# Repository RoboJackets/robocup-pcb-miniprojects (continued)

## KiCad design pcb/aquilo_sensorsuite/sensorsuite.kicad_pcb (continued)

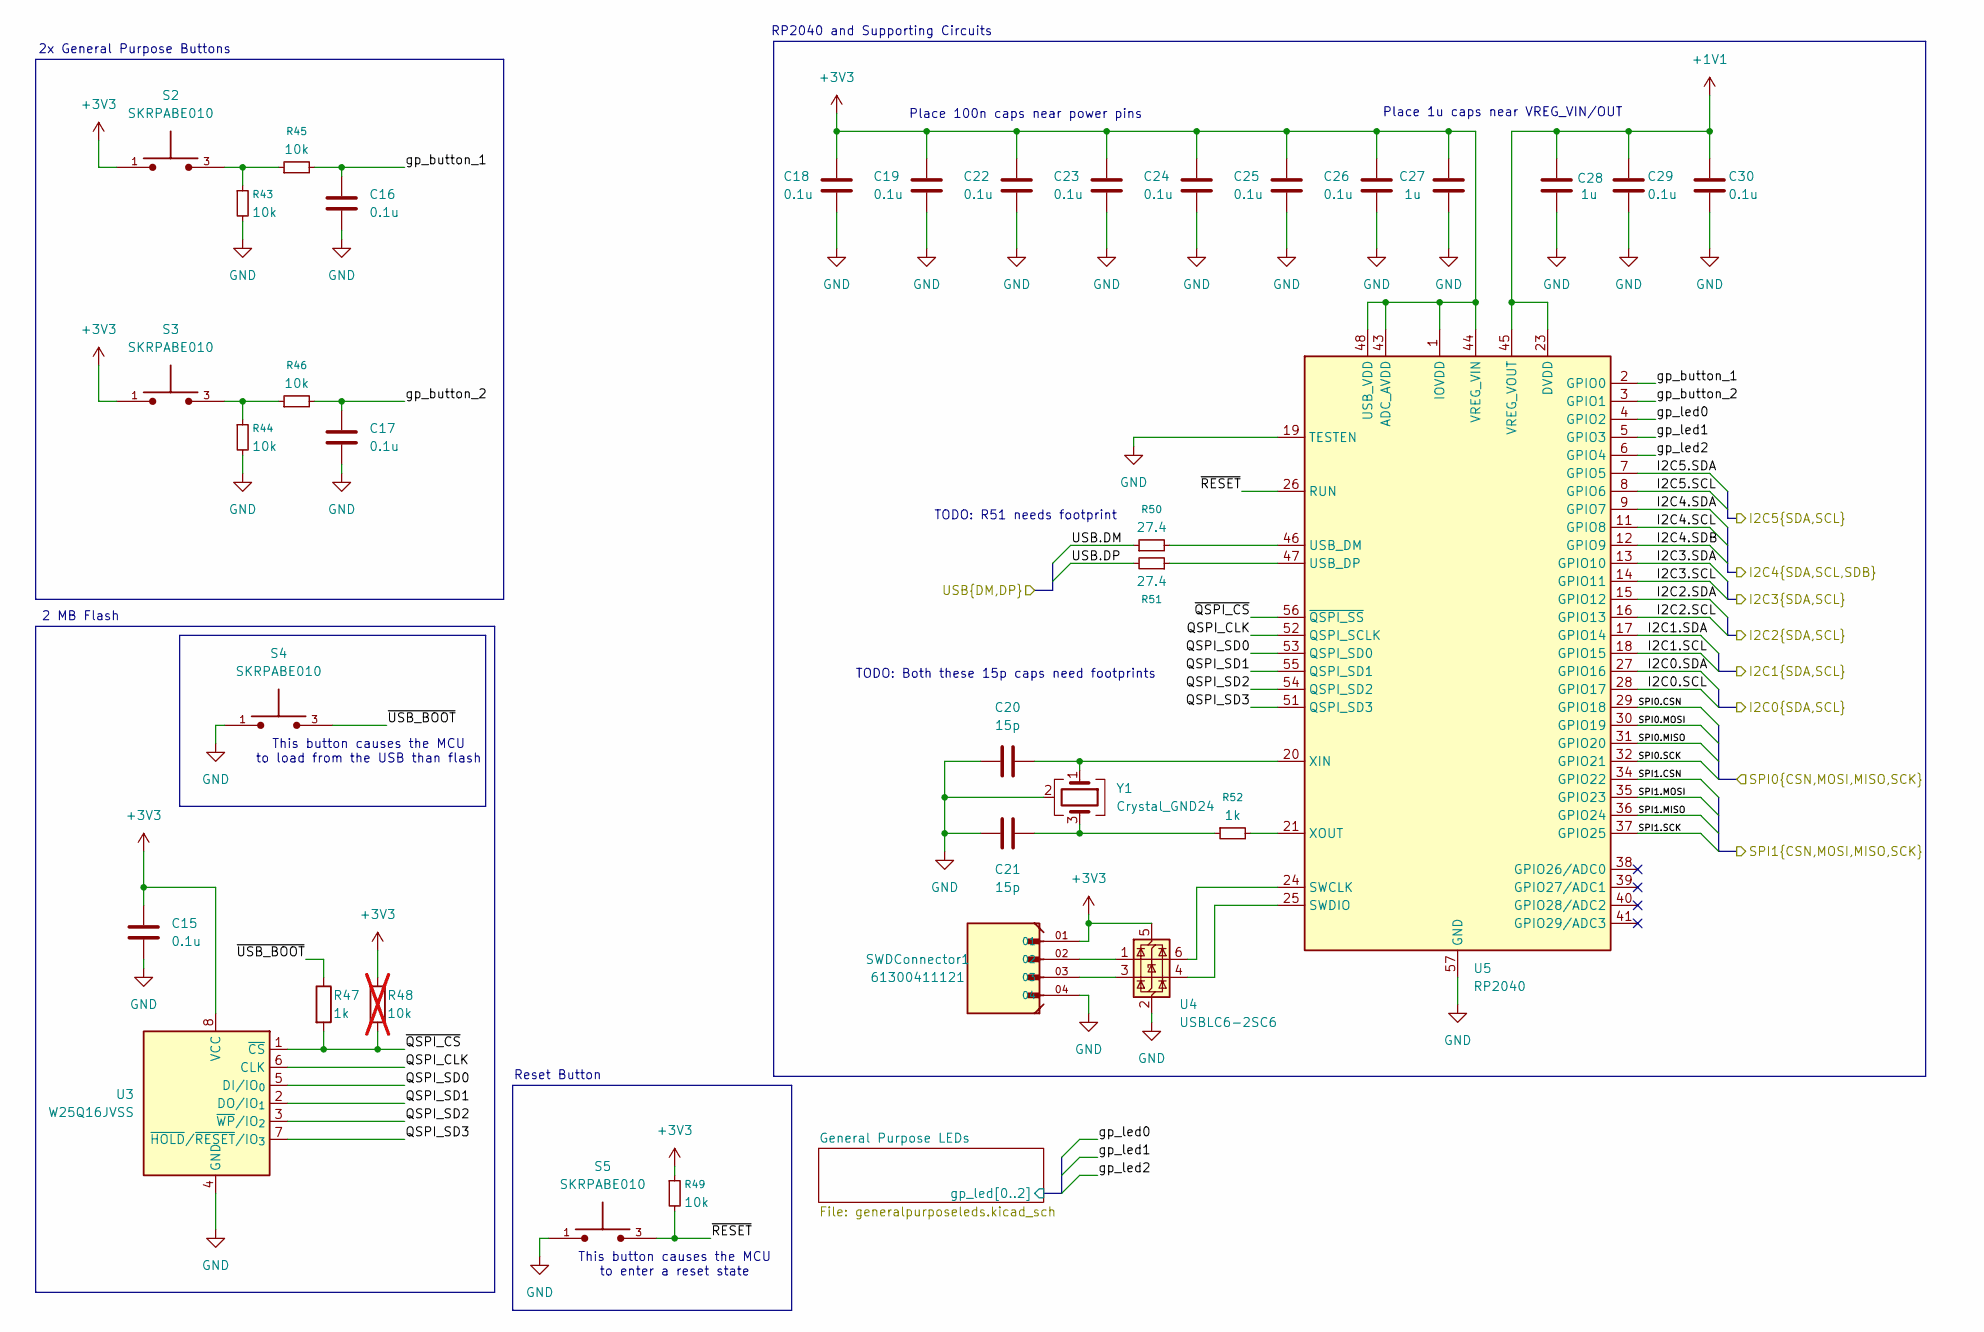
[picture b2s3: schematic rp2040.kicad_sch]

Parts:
C15, C16, C17, C18, C19, C22, C23, C24, C25, C26, C29, C30: 0.1u; C_0402_1005Metric; Manufacturer P/N 0402B104K160HI
C20, C21: 15p; C_0402_1005Metric; Manufacturer P/N GRM1555C1H150JA01D
C27, C28: 1u; C_0402_1005Metric; Manufacturer P/N 0402W105M6R3HI
R43, R44, R45, R46, R49: 10k; R_0402_1005Metric; Manufacturer P/N RK73H1ETTP1002F
R47, R52: 1k; R_0402_1005Metric; Manufacturer P/N RK73H1ETTP1001F
R48: 10k; R_0402_1005Metric; Manufacturer P/N RK73H1ETTP1002F; not fitted
R50, R51: 27.4; R_0402_1005Metric; Manufacturer P/N RC0402FR-0727R4L
S2, S3, S4, S5: SKRPABE010; SW_SKRPABE010; Manufacturer P/N SKRPABE010
SWDConnector1: 61300411121; WURTH_61300411121; Manufacturer P/N 61300411121
U3: W25Q16JVSS; SOIC-8_5.3x5.3mm_P1.27mm; Manufacturer P/N W25Q16JVUXIQ TR
U4: USBLC6-2SC6; SOT-23-6; Manufacturer P/N USBLC6-2SC6
U5: RP2040; QFN-56-1EP_7x7mm_P0.4mm_EP3.2x3.2mm; Manufacturer P/N SC0914(13)
Y1: Crystal_GND24; Crystal_SMD_Abracon_ABM8AIG-4Pin_3.2x2.5mm; Manufacturer P/N ABM8-272-T3

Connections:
+1V1: C28.1, C29.1, C30.1, U5.23 (DVDD), U5.45 (VREG_VOUT), U5.50 (DVDD)
+3V3: C15.1, C18.1, C19.1, C22.1, C23.1, C24.1, C25.1, C26.1, C27.1, R48.1, R49.1, S2.1, S2.2, S3.1, S3.2, SWDConnector1.01, U3.8 (VCC), U4.5 (VBUS), U5.1 (IOVDD), U5.10 (IOVDD), U5.22 (IOVDD), U5.33 (IOVDD), U5.42 (IOVDD), U5.43 (ADC_AVDD), U5.44 (VREG_VIN), U5.48 (USB_VDD), U5.49 (IOVDD); also elsewhere on the board
/Color Sensor/I2C0.SCL: U5.28 (GPIO17); also elsewhere on the board
/Color Sensor/I2C0.SDA: U5.27 (GPIO16); also elsewhere on the board
/GPIO Expander/I2C2.SCL: U5.16 (GPIO13); also elsewhere on the board
/GPIO Expander/I2C2.SDA: U5.15 (GPIO12); also elsewhere on the board
/Hall Effect Sensor/I2C3.SCL: U5.14 (GPIO11); also elsewhere on the board
/Hall Effect Sensor/I2C3.SDA: U5.13 (GPIO10); also elsewhere on the board
/IMU/I2C5.SCL: U5.8 (GPIO6); also elsewhere on the board
/IMU/I2C5.SDA: U5.7 (GPIO5); also elsewhere on the board
/LED Controller/I2C4.SCL: U5.11 (GPIO8); also elsewhere on the board
/LED Controller/I2C4.SDA: U5.9 (GPIO7); also elsewhere on the board
/LED Controller/I2C4.SDB: U5.12 (GPIO9); also elsewhere on the board
/Power/SPI0.CSN: U5.29 (GPIO18); also elsewhere on the board
/Power/SPI0.MISO: U5.31 (GPIO20); also elsewhere on the board
/Power/SPI0.MOSI: U5.30 (GPIO19); also elsewhere on the board
/Power/SPI0.SCK: U5.32 (GPIO21); also elsewhere on the board
/Power/SPI1.CSN: U5.34 (GPIO22); also elsewhere on the board
/Power/SPI1.MISO: U5.36 (GPIO24); also elsewhere on the board
/Power/SPI1.MOSI: U5.35 (GPIO23); also elsewhere on the board
/Power/SPI1.SCK: U5.37 (GPIO25); also elsewhere on the board
/Power/USB.DM: R50.1; also elsewhere on the board
/Power/USB.DP: R51.2; also elsewhere on the board
/Temperature Sensor/I2C1.SCL: U5.18 (GPIO15); also elsewhere on the board
/Temperature Sensor/I2C1.SDA: U5.17 (GPIO14); also elsewhere on the board
/rp2040/General Purpose LEDs/gp_led0: U5.4 (GPIO2); also elsewhere on the board
/rp2040/General Purpose LEDs/gp_led1: U5.5 (GPIO3); also elsewhere on the board
/rp2040/General Purpose LEDs/gp_led2: U5.6 (GPIO4); also elsewhere on the board
/rp2040/QSPI_CLK: U3.6 (CLK), U5.52 (QSPI_SCLK)
/rp2040/QSPI_SD0: U3.5 (DI/IO_{0}), U5.53 (QSPI_SD0)
/rp2040/QSPI_SD1: U3.2 (DO/IO_{1}), U5.55 (QSPI_SD1)
/rp2040/QSPI_SD2: U3.3 (~WP/IO_{2}), U5.54 (QSPI_SD2)
/rp2040/QSPI_SD3: U3.7 (~HOLD/~RESET/IO_{3}), U5.51 (QSPI_SD3)
/rp2040/gp_button_1: C16.1, R45.2, U5.2 (GPIO0)
/rp2040/gp_button_2: C17.1, R46.2, U5.3 (GPIO1)
/rp2040/~QSPI_CS: R47.2, R48.2, U3.1 (~CS), U5.56 (~QSPI_SS)
/rp2040/~RESET: R49.2, S5.3, S5.4, U5.26 (RUN)
/rp2040/~USB_BOOT: R47.1, S4.3, S4.4
GND: C15.2, C16.2, C17.2, C18.2, C19.2, C20.1, C21.1, C22.2, C23.2, C24.2, C25.2, C26.2, C27.2, C28.2, C29.2, C30.2, R43.2, R44.2, S4.1, S4.2, S5.1, S5.2, SWDConnector1.04, U3.4 (GND), U4.2 (GND), U5.19 (TESTEN), U5.57 (GND), Y1.2 (G), Y1.4 (G); also elsewhere on the board
unnamed: C21.2, R52.1, Y1.3
unnamed: R43.1, R45.1, S2.3, S2.4
unnamed: R44.1, R46.1, S3.3, S3.4
unnamed: SWDConnector1.02, U4.1 (I/O1)
unnamed: SWDConnector1.03, U4.3 (I/O2)
unnamed: U4.6 (I/O1), U5.24 (SWCLK)
unnamed: U4.4 (I/O2), U5.25 (SWDIO)
unnamed: R50.2, U5.46 (USB_DM)
unnamed: R51.1, U5.47 (USB_DP)
unnamed: C20.2, U5.20 (XIN), Y1.1
unnamed: R52.2, U5.21 (XOUT)

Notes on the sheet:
2x General Purpose Buttons
TODO: R51 needs footprint
Reset Button
This button causes the MCU to load from the USB than flash
TODO: Both these 15p caps need footprints
2 MB Flash
Place 1u caps near VREG_VIN/OUT
RP2040 and Supporting Circuits
This button causes the MCU to enter a reset state
Place 100n caps near power pins

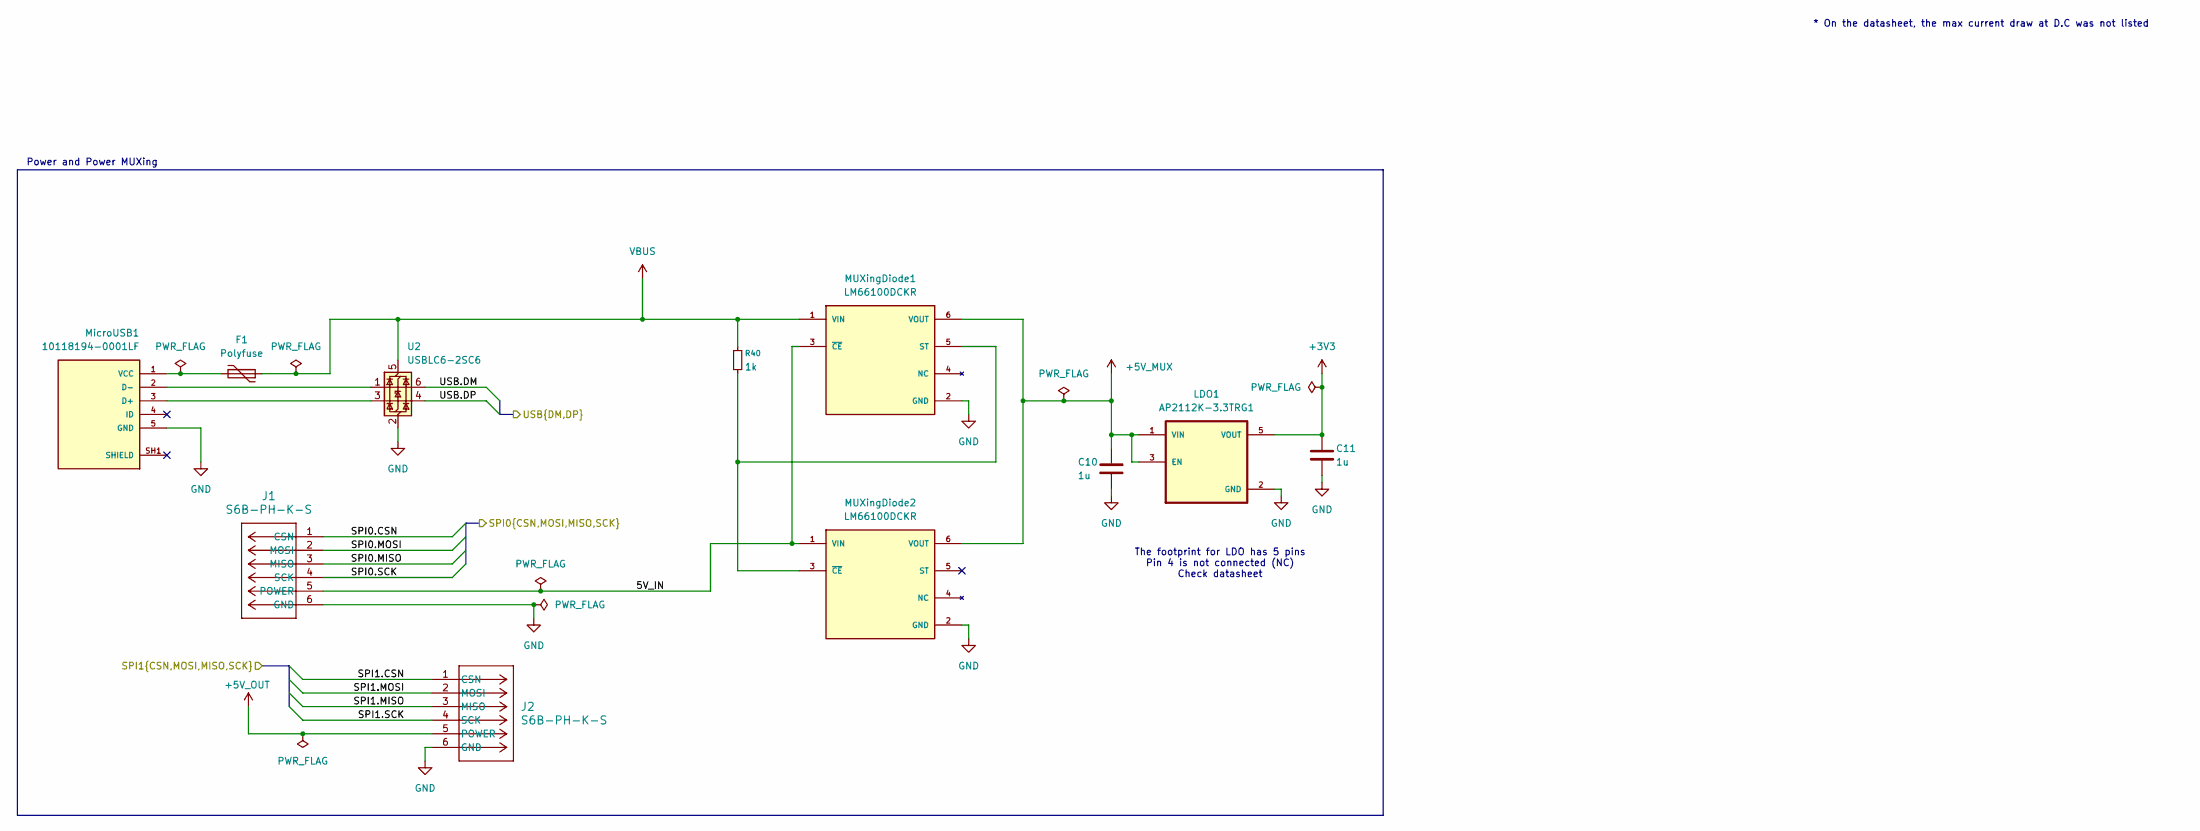
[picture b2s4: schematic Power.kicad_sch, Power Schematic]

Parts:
C10, C11: 1u; C_0402_1005Metric; Manufacturer P/N 0402W105M6R3HI
F1: Polyfuse; Fuse_1206_3216Metric; Manufacturer P/N MPTS1206L050
J1, J2: S6B-PH-K-S; JST_S6B-PH-K-S_LF__SN_; Manufacturer P/N S6B-PH-K-S
LDO1: AP2112K-3.3TRG1; SOT95P285X140-5N; Manufacturer P/N AP2112K-3.3TRG1
MUXingDiode1, MUXingDiode2: LM66100DCKR; SOT65P210X110-6N; Manufacturer P/N LM66100DCKR
MicroUSB1: 10118194-0001LF; AMPHENOL_10118194-0001LF; Manufacturer P/N 10118194-0001LF
R40: 1k; R_0402_1005Metric; Manufacturer P/N RK73H1ETTP1001F
U2: USBLC6-2SC6; SOT-23-6; Manufacturer P/N USBLC6-2SC6

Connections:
+3V3: C11.1, LDO1.5 (VOUT); also elsewhere on the board
+5V_MUX: C10.1, LDO1.1 (VIN), LDO1.3 (EN), MUXingDiode1.6 (VOUT), MUXingDiode2.6 (VOUT)
+5V_OUT: J2.5 (POWER)
/Power/5V_IN: J1.5 (POWER), MUXingDiode1.3 (~CE), MUXingDiode2.1 (VIN)
/Power/SPI0.CSN: J1.1 (CSN); also elsewhere on the board
/Power/SPI0.MISO: J1.3 (MISO); also elsewhere on the board
/Power/SPI0.MOSI: J1.2 (MOSI); also elsewhere on the board
/Power/SPI0.SCK: J1.4 (SCK); also elsewhere on the board
/Power/SPI1.CSN: J2.1 (CSN); also elsewhere on the board
/Power/SPI1.MISO: J2.3 (MISO); also elsewhere on the board
/Power/SPI1.MOSI: J2.2 (MOSI); also elsewhere on the board
/Power/SPI1.SCK: J2.4 (SCK); also elsewhere on the board
/Power/USB.DM: U2.6 (I/O1); also elsewhere on the board
/Power/USB.DP: U2.4 (I/O2); also elsewhere on the board
GND: C10.2, C11.2, J1.6 (GND), J2.6 (GND), LDO1.2 (GND), MUXingDiode1.2 (GND), MUXingDiode2.2 (GND), MicroUSB1.5 (GND), U2.2 (GND); also elsewhere on the board
unnamed: MUXingDiode1.5 (ST), MUXingDiode2.3 (~CE), R40.2
unnamed: MicroUSB1.3 (D+), U2.3 (I/O2)
unnamed: MicroUSB1.2 (D-), U2.1 (I/O1)
unnamed: F1.2, MicroUSB1.1 (VCC)
VBUS: F1.1, MUXingDiode1.1 (VIN), R40.1, U2.5 (VBUS)

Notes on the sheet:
The footprint for LDO has 5 pins Pin 4 is not connected (NC) Check datasheet
Power and Power MUXing
* On the datasheet, the max current draw at D.C was not listed

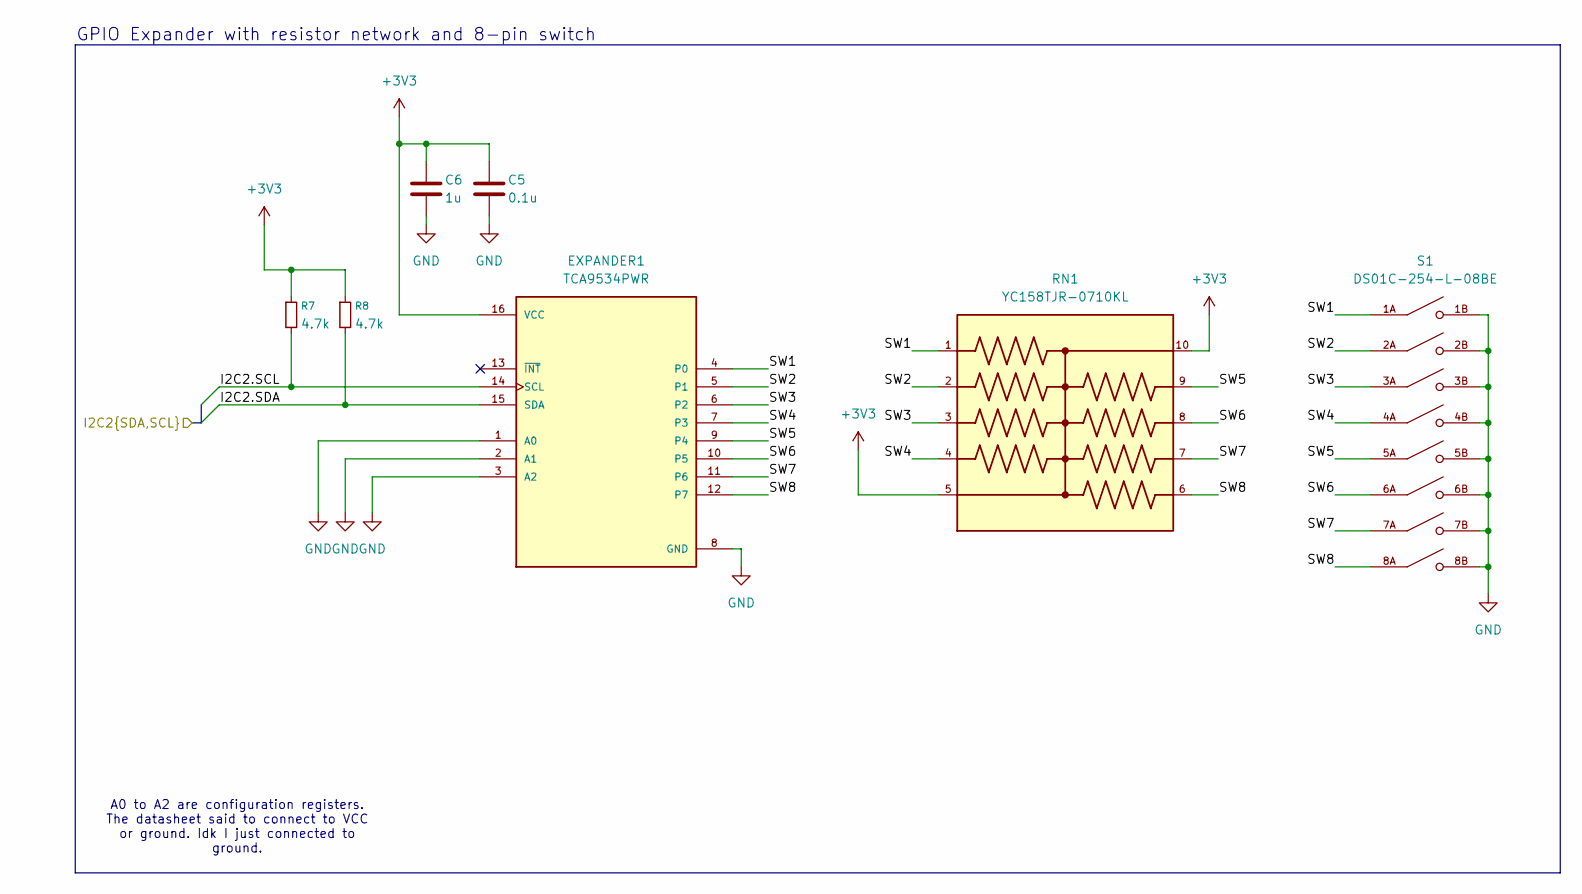
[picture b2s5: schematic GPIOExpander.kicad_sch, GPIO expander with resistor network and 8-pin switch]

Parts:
C5: 0.1u; C_0402_1005Metric; Manufacturer P/N 0402B104K160HI
C6: 1u; C_0402_1005Metric; Manufacturer P/N 0402W105M6R3HI
EXPANDER1: TCA9534PWR; SOP65P640X120-16N; Manufacturer P/N TCA9534PWR
R7, R8: 4.7k; R_0402_1005Metric; Manufacturer P/N RK73H1ETTP4701F
RN1: YC158TJR-0710KL; RESCAXE64P320X160X70-10N; Manufacturer P/N YC158TJR-0710KL
S1: DS01C-254-L-08BE; SW_DS01C-254-L-08BE; Manufacturer P/N DS01C-254-L-08BE

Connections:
+3V3: C5.1, C6.1, EXPANDER1.16 (VCC), R7.1, R8.1, RN1.5, RN1.10; also elsewhere on the board
/GPIO Expander/I2C2.SCL: EXPANDER1.14 (SCL), R7.2; also elsewhere on the board
/GPIO Expander/I2C2.SDA: EXPANDER1.15 (SDA), R8.2; also elsewhere on the board
/GPIO Expander/SW1: EXPANDER1.4 (P0), RN1.1, S1.1A
/GPIO Expander/SW2: EXPANDER1.5 (P1), RN1.2, S1.2A
/GPIO Expander/SW3: EXPANDER1.6 (P2), RN1.3, S1.3A
/GPIO Expander/SW4: EXPANDER1.7 (P3), RN1.4, S1.4A
/GPIO Expander/SW5: EXPANDER1.9 (P4), RN1.9, S1.5A
/GPIO Expander/SW6: EXPANDER1.10 (P5), RN1.8, S1.6A
/GPIO Expander/SW7: EXPANDER1.11 (P6), RN1.7, S1.7A
/GPIO Expander/SW8: EXPANDER1.12 (P7), RN1.6, S1.8A
GND: C5.2, C6.2, EXPANDER1.1 (A0), EXPANDER1.2 (A1), EXPANDER1.3 (A2), EXPANDER1.8 (GND), S1.1B, S1.2B, S1.3B, S1.4B, S1.5B, S1.6B, S1.7B, S1.8B; also elsewhere on the board

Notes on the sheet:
A0 to A2 are configuration registers. The datasheet said to connect to VCC or ground. Idk I just connected to ground.
GPIO Expander with resistor network and 8-pin switch

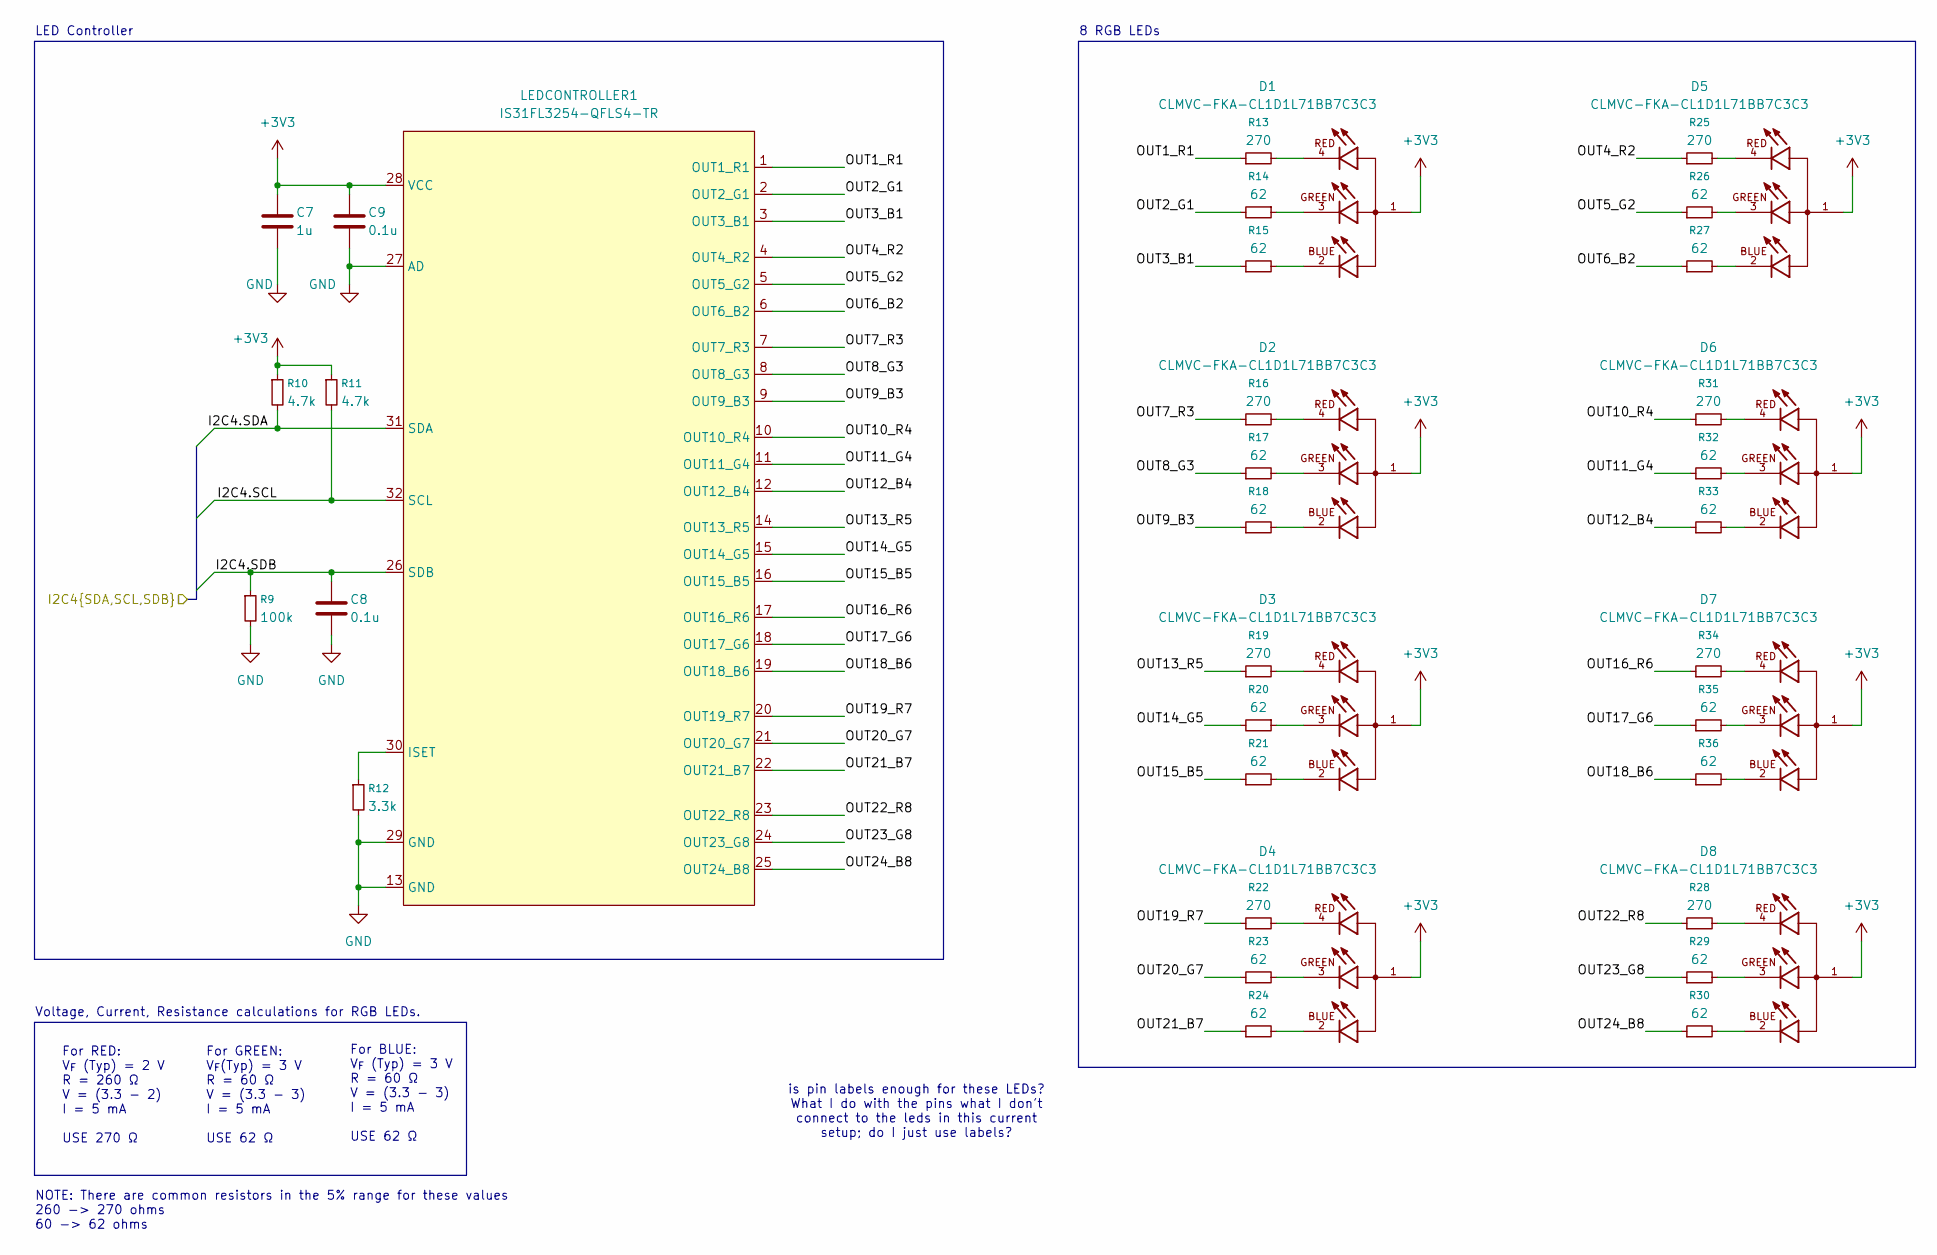
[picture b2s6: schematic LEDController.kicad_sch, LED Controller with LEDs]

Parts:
C7: 1u; C_0402_1005Metric; Manufacturer P/N 0402W105M6R3HI
C8, C9: 0.1u; C_0402_1005Metric; Manufacturer P/N 0402B104K160HI
D1, D2, D3, D4, D5, D6, D7, D8: CLMVC-FKA-CL1D1L71BB7C3C3; LED_CLMVC-FKA-CL1D1L71BB7C3C3; Manufacturer P/N CLMVC-FKA-CL1D1L71BB7C3C3
LEDCONTROLLER1: IS31FL3254-QFLS4-TR; 0; Manufacturer P/N IS31FL3254-QFLS4-TR
R9: 100k; R_0402_1005Metric; Manufacturer P/N ERJ-2GEJ104X
R10, R11: 4.7k; R_0402_1005Metric; Manufacturer P/N RK73H1ETTP4701F
R12: 3.3k; R_0402_1005Metric; Manufacturer P/N RC0402JR-073K3L
R13, R16, R19, R22, R25, R28, R31, R34: 270; R_0402_1005Metric; Manufacturer P/N ERJ-2GEJ271X
R14, R15, R17, R18, R20, R21, R23, R24, R26, R27, R29, R30, R32, R33, R35, R36: 62; R_0402_1005Metric; Manufacturer P/N ERJ-2GEJ620X

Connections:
+3V3: C7.1, C9.1, D1.1, D2.1, D3.1, D4.1, D5.1, D6.1, D7.1, D8.1, LEDCONTROLLER1.28 (VCC), R10.1, R11.1; also elsewhere on the board
/LED Controller/I2C4.SCL: LEDCONTROLLER1.32 (SCL), R11.2; also elsewhere on the board
/LED Controller/I2C4.SDA: LEDCONTROLLER1.31 (SDA), R10.2; also elsewhere on the board
/LED Controller/I2C4.SDB: C8.1, LEDCONTROLLER1.26 (SDB), R9.1; also elsewhere on the board
/LED Controller/OUT1_R1: LEDCONTROLLER1.1 (OUT1_R1), R13.1
/LED Controller/OUT2_G1: LEDCONTROLLER1.2 (OUT2_G1), R14.2
/LED Controller/OUT3_B1: LEDCONTROLLER1.3 (OUT3_B1), R15.1
/LED Controller/OUT4_R2: LEDCONTROLLER1.4 (OUT4_R2), R25.1
/LED Controller/OUT5_G2: LEDCONTROLLER1.5 (OUT5_G2), R26.1
/LED Controller/OUT6_B2: LEDCONTROLLER1.6 (OUT6_B2), R27.1
/LED Controller/OUT7_R3: LEDCONTROLLER1.7 (OUT7_R3), R16.1
/LED Controller/OUT8_G3: LEDCONTROLLER1.8 (OUT8_G3), R17.1
/LED Controller/OUT9_B3: LEDCONTROLLER1.9 (OUT9_B3), R18.1
/LED Controller/OUT10_R4: LEDCONTROLLER1.10 (OUT10_R4), R31.1
/LED Controller/OUT11_G4: LEDCONTROLLER1.11 (OUT11_G4), R32.1
/LED Controller/OUT12_B4: LEDCONTROLLER1.12 (OUT12_B4), R33.1
/LED Controller/OUT13_R5: LEDCONTROLLER1.14 (OUT13_R5), R19.1
/LED Controller/OUT14_G5: LEDCONTROLLER1.15 (OUT14_G5), R20.2
/LED Controller/OUT15_B5: LEDCONTROLLER1.16 (OUT15_B5), R21.1
/LED Controller/OUT16_R6: LEDCONTROLLER1.17 (OUT16_R6), R34.1
/LED Controller/OUT17_G6: LEDCONTROLLER1.18 (OUT17_G6), R35.1
/LED Controller/OUT18_B6: LEDCONTROLLER1.19 (OUT18_B6), R36.1
/LED Controller/OUT19_R7: LEDCONTROLLER1.20 (OUT19_R7), R22.1
/LED Controller/OUT20_G7: LEDCONTROLLER1.21 (OUT20_G7), R23.1
/LED Controller/OUT21_B7: LEDCONTROLLER1.22 (OUT21_B7), R24.1
/LED Controller/OUT22_R8: LEDCONTROLLER1.23 (OUT22_R8), R28.1
/LED Controller/OUT23_G8: LEDCONTROLLER1.24 (OUT23_G8), R29.1
/LED Controller/OUT24_B8: LEDCONTROLLER1.25 (OUT24_B8), R30.1
GND: C7.2, C8.2, C9.2, LEDCONTROLLER1.13 (GND), LEDCONTROLLER1.27 (AD), LEDCONTROLLER1.29 (GND), R9.2, R12.2; also elsewhere on the board
unnamed: D1.2, R15.2
unnamed: D1.3, R14.1
unnamed: D1.4, R13.2
unnamed: D2.2, R18.2
unnamed: D2.3, R17.2
unnamed: D2.4, R16.2
unnamed: D3.2, R21.2
unnamed: D3.3, R20.1
unnamed: D3.4, R19.2
unnamed: D4.2, R24.2
unnamed: D4.3, R23.2
unnamed: D4.4, R22.2
unnamed: D5.2, R27.2
unnamed: D5.3, R26.2
unnamed: D5.4, R25.2
unnamed: D6.2, R33.2
unnamed: D6.3, R32.2
unnamed: D6.4, R31.2
unnamed: D7.2, R36.2
unnamed: D7.3, R35.2
unnamed: D7.4, R34.2
unnamed: D8.2, R30.2
unnamed: D8.3, R29.2
unnamed: D8.4, R28.2
unnamed: LEDCONTROLLER1.30 (ISET), R12.1

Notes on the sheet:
For BLUE: V_{F} (Typ) = 3 V R = 60 Ω V = (3.3 - 3) I = 5 mA USE 62 Ω
LED Controller
is pin labels enough for these LEDs? What I do with the pins what I don't connect to the leds in this current setup; do I just use labels?
For RED: V_{F} (Typ) = 2 V R = 260 Ω V = (3.3 - 2) I = 5 mA USE 270 Ω
For GREEN: V_{F}(Typ) = 3 V R = 60 Ω V = (3.3 - 3) I = 5 mA USE 62 Ω
NOTE: There are common resistors in the 5% range for these values 260 -> 270 ohms 60 -> 62 ohms
8 RGB LEDs
Voltage, Current, Resistance calculations for RGB LEDs.

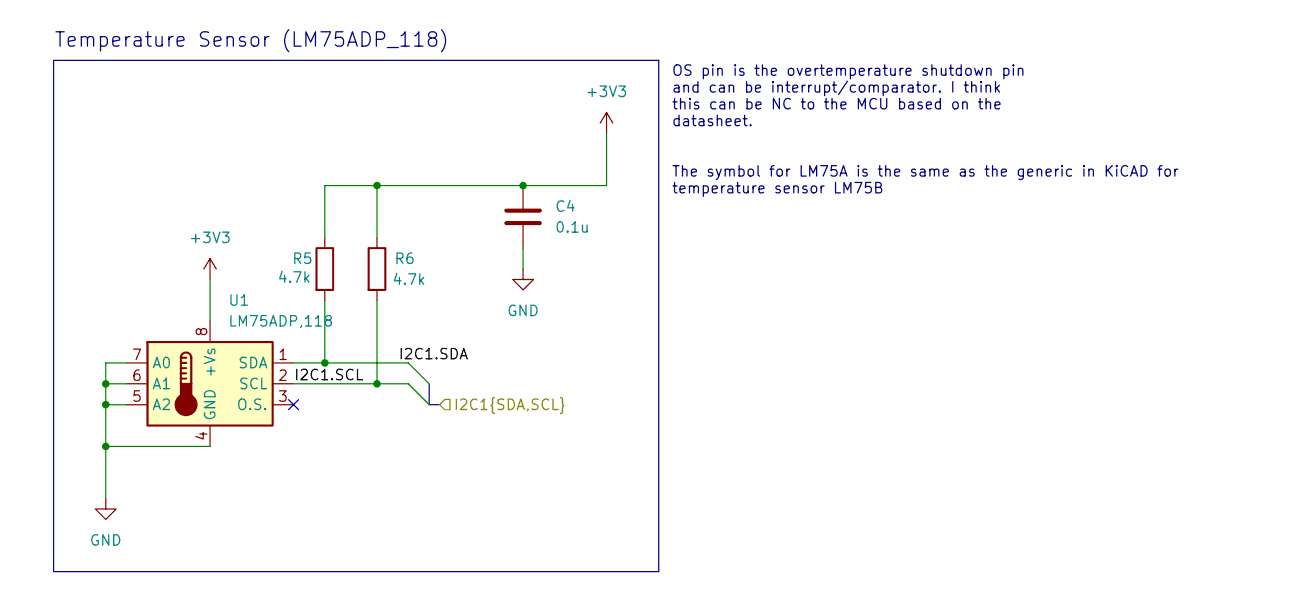
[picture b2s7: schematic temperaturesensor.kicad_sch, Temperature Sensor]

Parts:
C4: 0.1u; C_0402_1005Metric; Manufacturer P/N 0402B104K160HI
R5, R6: 4.7k; R_0402_1005Metric; Manufacturer P/N RK73H1ETTP4701F
U1: LM75ADP,118; SOP65P490X110-8N; Manufacturer P/N LM75ADP,118

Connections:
+3V3: C4.1, R5.1, R6.1, U1.8 (+Vs); also elsewhere on the board
/Temperature Sensor/I2C1.SCL: R6.2, U1.2 (SCL); also elsewhere on the board
/Temperature Sensor/I2C1.SDA: R5.2, U1.1 (SDA); also elsewhere on the board
GND: C4.2, U1.4 (GND), U1.5 (A2), U1.6 (A1), U1.7 (A0); also elsewhere on the board

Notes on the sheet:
OS pin is the overtemperature shutdown pin and can be interrupt/comparator. I think this can be NC to the MCU based on the datasheet. The symbol for LM75A is the same as the generic in KiCAD for temperature sensor LM75B
Temperature Sensor (LM75ADP_118)

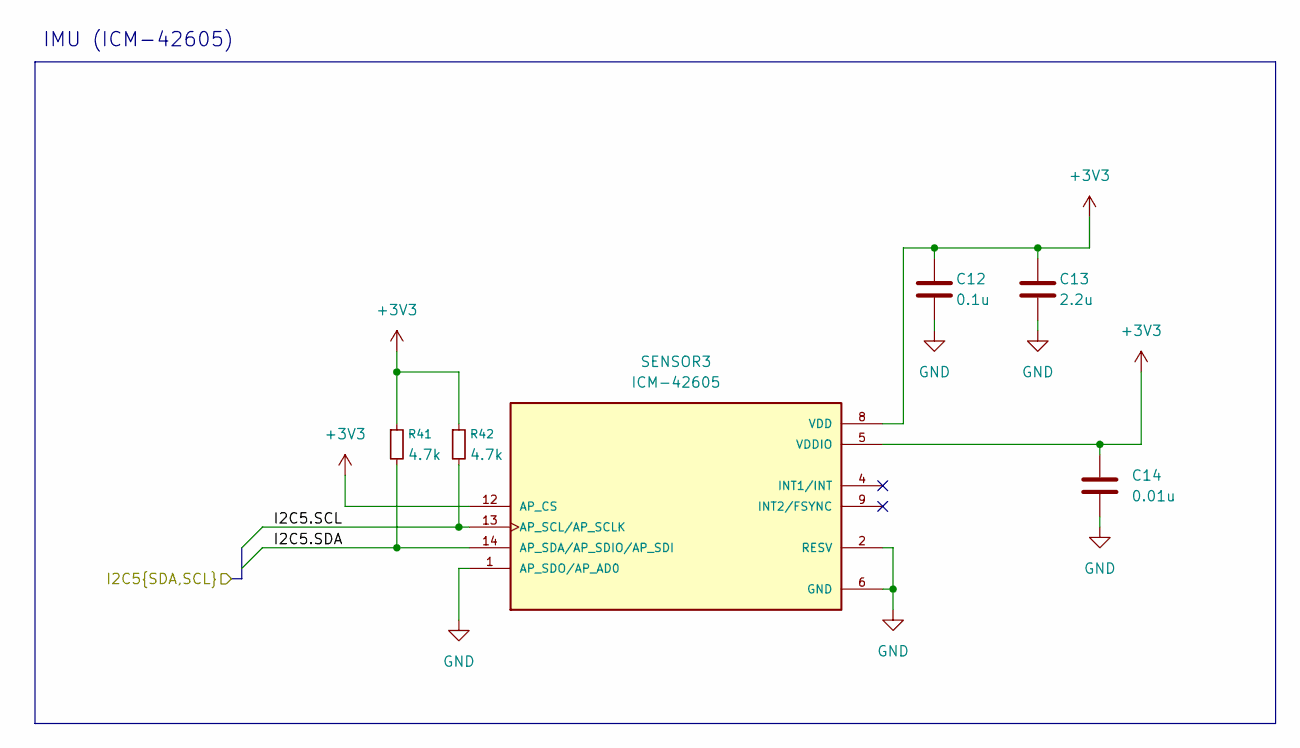
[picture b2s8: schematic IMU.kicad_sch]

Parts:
C12: 0.1u; C_0402_1005Metric; Manufacturer P/N 0402B104K160HI
C13: 2.2u; C_0402_1005Metric; Manufacturer P/N 0402W225K100HI
C14: 0.01u; C_0402_1005Metric; Manufacturer P/N 0402B103K500HI
R41, R42: 4.7k; R_0402_1005Metric; Manufacturer P/N RK73H1ETTP4701F
SENSOR3: ICM-42605; XDCR_ICM-42605; Manufacturer P/N 1428-1152-2-ND

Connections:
+3V3: C12.1, C13.1, C14.1, R41.1, R42.1, SENSOR3.5 (VDDIO), SENSOR3.8 (VDD), SENSOR3.12 (AP_CS); also elsewhere on the board
/IMU/I2C5.SCL: R42.2, SENSOR3.13 (AP_SCL/AP_SCLK); also elsewhere on the board
/IMU/I2C5.SDA: R41.2, SENSOR3.14 (AP_SDA/AP_SDIO/AP_SDI); also elsewhere on the board
GND: C12.2, C13.2, C14.2, SENSOR3.1 (AP_SDO/AP_AD0), SENSOR3.2 (RESV), SENSOR3.3 (RESV), SENSOR3.6 (GND), SENSOR3.7 (RESV), SENSOR3.10 (RESV), SENSOR3.11 (RESV); also elsewhere on the board

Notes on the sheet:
IMU (ICM-42605)

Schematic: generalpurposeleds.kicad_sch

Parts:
D9, D10, D11: SML-310LTT86; LED_SML-310_ROM; Manufacturer P/N CLMVC-FKA-CL1D1L71BB7C3C3
R37, R38, R39: 1k; R_0402_1005Metric; Manufacturer P/N RK73H1ETTP1001F

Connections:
/rp2040/General Purpose LEDs/gp_led0: R37.1; also elsewhere on the board
/rp2040/General Purpose LEDs/gp_led1: R38.1; also elsewhere on the board
/rp2040/General Purpose LEDs/gp_led2: R39.1; also elsewhere on the board
GND: D9.1, D10.1, D11.1; also elsewhere on the board
unnamed: D9.2, R37.2
unnamed: D10.2, R38.2
unnamed: D11.2, R39.2

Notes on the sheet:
V_{F}(Typ)= 1.75 V R = 77.5 Ω V = (3.3 - 1.75) I = 20 mA 77.5 Ω is an uncommon resistor, maybe change to something else V_{F}(Typ)= 1.75 V R = 330 Ω V = (3.3 - 1.75) I = 4.7 mA For a status LED, 330 Ω (about 4.7 mA) should be sufficient. It's bright enough for most indicator LEDs and stays well wit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
3x General Purpose RED LEDs
Output drive strength from the pads (Each GPIO is connected to the off-chip world via a "pad") can only be set to 2, 4, 8, 12 mA. Since the typical amps for these LEDs are 20 mA, we can take 12 mA as the ceiling amperage.

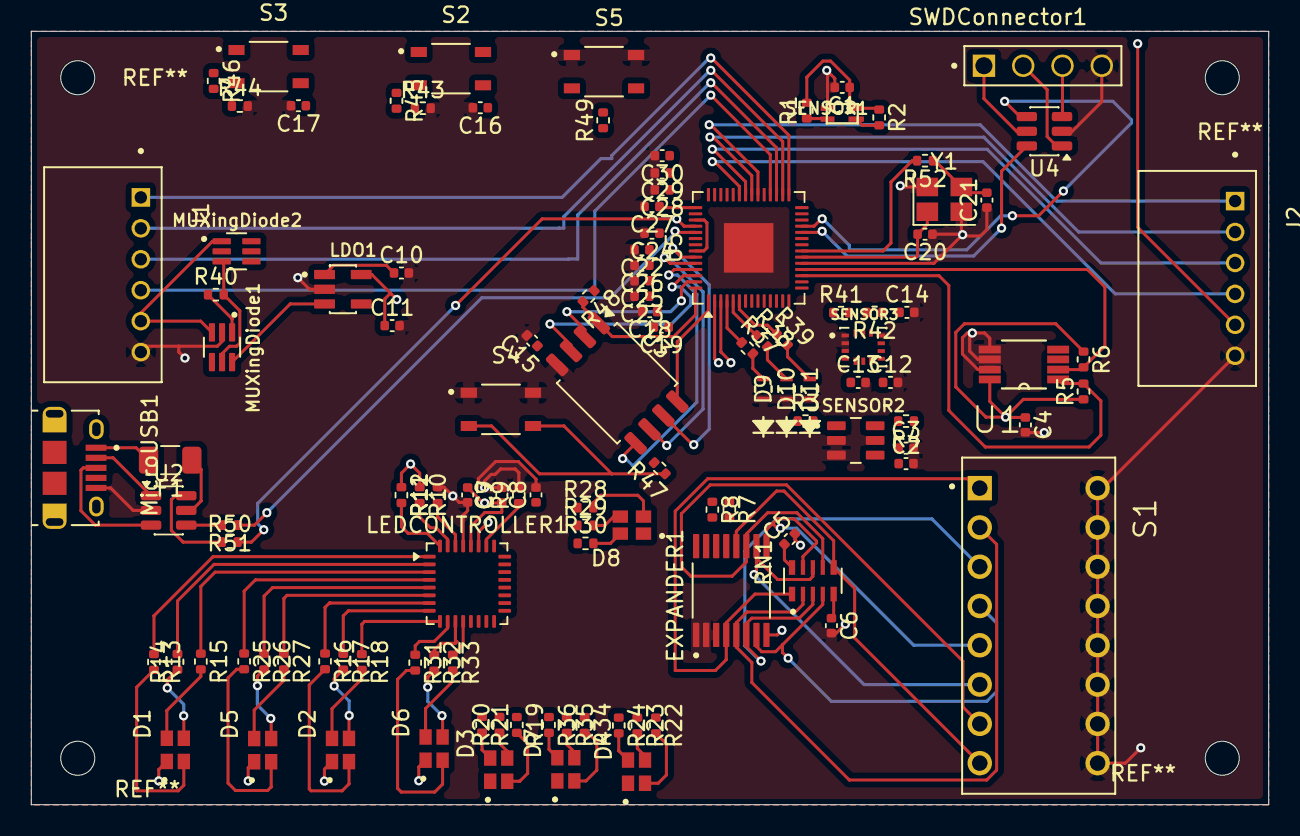
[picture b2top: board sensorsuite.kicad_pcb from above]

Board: 4 copper layers, 80.0 x 50.0 mm, 118 parts (0 on the bottom side), 117 nets.
